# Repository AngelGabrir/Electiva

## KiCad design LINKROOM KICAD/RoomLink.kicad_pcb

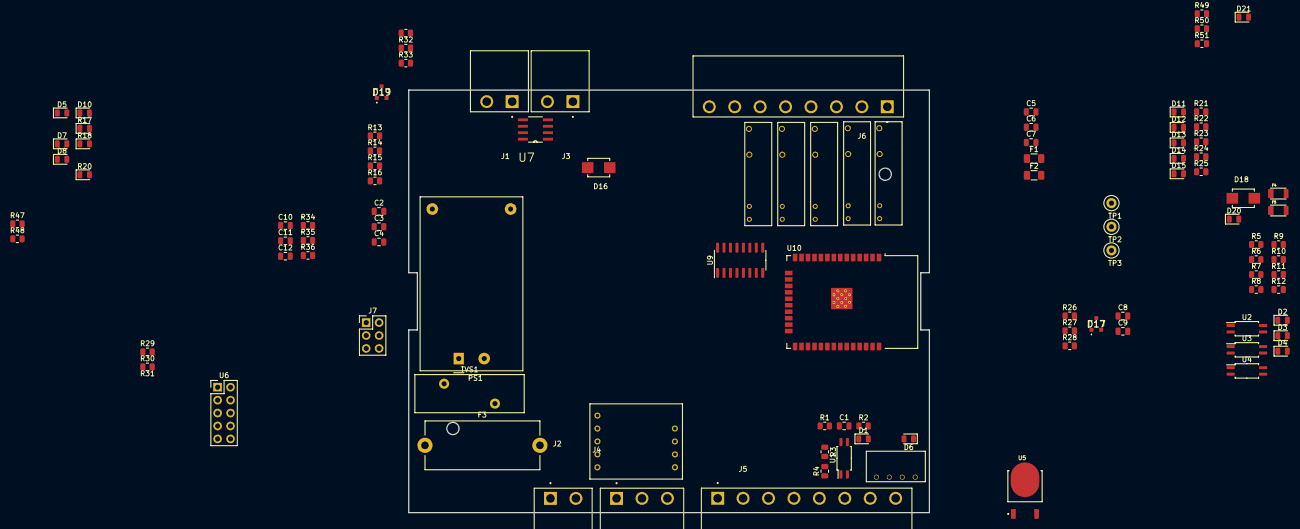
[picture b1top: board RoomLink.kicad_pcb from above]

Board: 4 copper layers, 102.4 x 83.1 mm, 105 parts (0 on the bottom side), 88 nets, no tracks yet.

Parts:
C1, C2, C3, C4, C10, C12: 0.1uF; C_0805_2012Metric
C5: 0.33uF/25V; C_0805_2012Metric
C6: 2.2uF/25V; C_0805_2012Metric
C7: 47uF/10V; C_0805_2012Metric
C8: 1uF/25V; C_0805_2012Metric
C9: 0.1uF/50V; C_0805_2012Metric
C11: 22uF; C_0805_2012Metric
D1, D2, D3, D4, D11, D12, D13, D14, D15, D20: LED; LED_0805_2012Metric
D5, D6: 1SMA5918BT3G; D_0805_2012Metric
D7, D8, D10, D21: LED; D_0805_2012Metric
D16, D18: SMBJ12CA; DIOM4336X265N
D17, D19: SM712-02HTG; SM71202HTG
F1, F2: PTS120660V010; Fuse_1206_3216Metric
F3: Fuse; Fuseholder_Cylinder-5x20mm_Stelvio-Kontek_PTF78_Horizontal_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
F4, F5: PTS120660V010; RESC3115X65N
J1, J2, J3: TBP04R12-500-02BE; CUI_TBP04R12-500-02BE
J4: TBP04R12-500-03GR; CUI_TBP04R12-500-03GR
J5, J6: TBP04R12-500-08GR; CUI_TBP04R12-500-08GR
J7: PinHeader_2x03_P2.54mm_Vertical
K1, K2, K3, K4, K5: AZ921
PS1: HLK-PM12; Converter_ACDC_HiLink_HLK-PMxx
R1, R7, R11, R15: 10K; R_0805_2012Metric
R2, R8, R12, R16, R47: 470; R_0805_2012Metric
R3, R5, R9, R13: 330; R_0805_2012Metric
R4, R6, R10, R14: 10; R_0805_2012Metric
R17, R18: R; D_0805_2012Metric
R20: 470; D_0805_2012Metric
R21, R22, R23, R24, R25: R; R_0805_2012Metric
R26, R27, R28: 10/1%; R_0805_2012Metric
R29, R30, R31, R32, R33: 2.2K; R_0805_2012Metric
R34, R35, R48, R49, R50: 100K; R_0805_2012Metric
R36: 22K; R_0805_2012Metric
R51: 1K; R_0805_2012Metric
TP1, TP2, TP3: TestPoint; TestPoint_Loop_D1.80mm_Drill1.0mm_Beaded
TVS1: RV_Disc_D21.5mm_W7.5mm_P10mm
U1, U2, U3, U4: FODM214; SOP-4_4.4x2.6mm_P1.27mm
U5: NJM2885DL1-33-TE1; DPAK228P968X238-4N
U6: PinHeader_2x05_P2.54mm_Vertical
U7: SP485ECN-L; SOIC127P600X175-8N
U8: TD521D485H-E
U9: ULN2003A; SOIC-16_3.9x9.9mm_P1.27mm
U10: ESP32-WROOM-32
U11: B0303S; B0505S-W2R2

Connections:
+3V3: D6.1 (A), R3.1, R5.1, R9.1, R13.1, U11.4 (OUT+)
+12V: C5.1, F2.2, K1.1, K2.1, K3.1, K4.1, K5.1, PS1.4 (+Vout), R21.2, R22.2, R23.2, R24.2, R25.2, TP3.1, U5.1 (VI)
/Smart-Control-HVAC/CON-A-: F4.2, J4.2
/Smart-Control-HVAC/CON-B+: F5.2, J4.3
/Smart-Control-HVAC/CON-DC+: F2.1, J1.1, R18.1
/Smart-Control-HVAC/CON-DC-: D8.1 (K), F1.1, J1.2
/Smart-Control-HVAC/CON-FAN1: J6.7, K3.4
/Smart-Control-HVAC/CON-FAN2: J6.6, K4.4
/Smart-Control-HVAC/CON-FAN3: J6.5, K5.4
/Smart-Control-HVAC/CON-FAN-C: J6.8, K3.3, K4.3, K5.3
/Smart-Control-HVAC/CON-IN1+: J5.8, U1.2
/Smart-Control-HVAC/CON-IN1-: J5.7, R4.1
/Smart-Control-HVAC/CON-IN2+: J5.6, U3.2
/Smart-Control-HVAC/CON-IN2-: J5.5, R10.1
/Smart-Control-HVAC/CON-IN3+: J5.4, U2.2
/Smart-Control-HVAC/CON-IN3-: J5.3, R6.1
/Smart-Control-HVAC/CON-IN4+: J5.2, U4.2
/Smart-Control-HVAC/CON-IN4-: J5.1, R14.1
/Smart-Control-HVAC/CON-L1: F3.1, J2.1
/Smart-Control-HVAC/CON-LCDA-: J3.1, R28.2
/Smart-Control-HVAC/CON-LCDB+: J3.2, R27.2
/Smart-Control-HVAC/CON-NEUT: J2.2, PS1.1 (AC/L), TVS1.2
/Smart-Control-HVAC/CON-OUT1A: J6.3, K1.4
/Smart-Control-HVAC/CON-OUT1B: J6.4, K1.3
/Smart-Control-HVAC/CON-OUT2A: J6.1, K2.4
/Smart-Control-HVAC/CON-OUT2B: J6.2, K2.3
/Smart-Control-HVAC/CONTROL/COM_RS485_LCD: R26.1, U10.6 (IO34)
/Smart-Control-HVAC/CONTROL/CON_RS485_eXT: U8.5 (CON), U10.7 (IO35)
/Smart-Control-HVAC/CONTROL/INPUT_1_MICRO: C1.1, D1.1 (K), R1.2, U1.4, U10.25 (IO0)
/Smart-Control-HVAC/CONTROL/INPUT_2_MICRO: C3.1, D3.1 (K), R11.2, U3.4, U10.29 (IO5)
/Smart-Control-HVAC/CONTROL/INPUT_3_MICRO: C2.1, D2.1 (K), R7.2, U2.4, U10.26 (IO4)
/Smart-Control-HVAC/CONTROL/INPUT_4_MICRO: C4.1, D4.1 (K), R15.2, U4.4, U10.24 (IO2)
/Smart-Control-HVAC/CONTROL/RLY_FAN1_MICRO: U9.5 (I5), U10.10 (IO25)
/Smart-Control-HVAC/CONTROL/RLY_FAN2_MICRO: U9.4 (I4), U10.11 (IO26)
/Smart-Control-HVAC/CONTROL/RLY_FAN3_MICRO: U9.3 (I3), U10.12 (IO27)
/Smart-Control-HVAC/CONTROL/RLY_OUT1_MICRO: U9.1 (I1), U10.36 (IO22)
/Smart-Control-HVAC/CONTROL/RLY_OUT2_MICRO: U9.2 (I2), U10.37 (IO23)
/Smart-Control-HVAC/CONTROL/Rx_RS485_eXT: U8.4 (RXD), U10.34 (RXD0/IO3)
/Smart-Control-HVAC/CONTROL/Rx_RS485_lcd: U7.4 (DI), U10.27 (IO16)
/Smart-Control-HVAC/CONTROL/Tx_RS485_LCD: U7.1 (RO), U10.28 (IO17)
/Smart-Control-HVAC/CONTROL/Tx_RS485_eXT: U8.3 (TXD), U10.35 (TXD0/IO1)
/Smart-Control-HVAC/RGND: D19.3, J4.1, R33.1, U8.10 (RGND)
EN: C10.2, R35.2, R36.2, U6.10 (EN), U10.3 (EN)
GND: C1.2, C2.2, C3.2, C4.2, C5.2, C6.2, C7.2, C8.2, C9.2, C11.2, C12.2, D5.2 (C), D6.2 (C), D7.1 (K), D10.1 (K), D17.3, F1.2, J7.5, PS1.3 (-Vout), TP2.1, U1.3, U2.3, U3.3, U4.3, U5.2 (GND), U6.3 (GND), U6.9 (GND), U7.5 (GND), U8.2 (GND), U9.8 (GND), U10.1 (GND), U10.15 (GND), U10.38 (GND), U10.39 (GND), U11.1 (IN-)
GNDA: R4.2, R6.2, R10.2, R14.2, U11.3 (OUT-)
MTCLK: R49.2, U6.4 (MTCLK), U10.16 (IO13)
MTD0: R50.2, U6.6 (MTD0), U10.23 (IO15)
MTD1: R34.2, U6.8 (MTD1), U10.14 (IO12)
MTMS: R48.2, U6.2 (MTMS), U10.13 (IO14)
unnamed: D1.2 (A), R2.2
unnamed: D2.2 (A), R8.2
unnamed: D3.2 (A), R12.2
unnamed: D4.2 (A), R16.2
unnamed: D7.2 (A), R17.2
unnamed: D8.2 (A), R18.2
unnamed: D10.2 (A), R20.2
unnamed: D11.2 (A), R21.1
unnamed: D11.1 (K), K1.2, U9.16 (O1)
unnamed: D12.2 (A), R22.1
unnamed: D12.1 (K), K2.2, U9.15 (O2)
unnamed: D13.2 (A), R23.1
unnamed: D13.1 (K), K3.2, U9.14 (O3)
unnamed: D14.2 (A), R24.1
unnamed: D14.1 (K), K4.2, U9.13 (O4)
unnamed: D15.2 (A), R25.1
unnamed: D15.1 (K), K5.2, U9.12 (O5)
unnamed: D20.2 (A), R29.2
unnamed: D21.2 (A), R47.1
unnamed: D21.1 (K), U10.9 (IO33)
unnamed: F4.1, R31.2
unnamed: F5.1, R32.2
unnamed: F3.2, PS1.2 (AC/N), TVS1.1
unnamed: R3.2, U1.1
unnamed: R5.2, U2.1
unnamed: R9.2, U3.1
unnamed: R13.2, U4.1
unnamed: R51.2, U6.1 (Vin)
unnamed: D16.1, D17.1, D17.2, R27.1, U7.6 (A)
unnamed: D16.2, R28.1, U7.7 (B)
unnamed: R26.2, U7.2 (~RE), U7.3 (DE)
unnamed: D18.2, D19.2, R30.2, R31.1, U8.9 (A)
unnamed: D18.1, D19.1, R32.1, R33.2, U8.8 (B)
unnamed: R29.1, R30.1, U8.7 (Vo)
unnamed: J7.2, U10.30 (IO18)
unnamed: J7.4, U10.31 (IO19)
unnamed: J7.6, U10.33 (IO21)
unnamed: J7.3, U10.8 (IO32)
VDD: C6.1, C7.1, C8.1, C9.1, C10.1, C11.1, C12.1, D5.1 (A), J7.1, R1.1, R2.1, R7.1, R8.1, R11.1, R12.1, R15.1, R16.1, R17.1, R20.1, R34.1, R35.1, R36.1, R47.2, R48.1, R49.1, R50.1, R51.1, TP1.1, U5.3 (VO), U7.8 (VCC), U8.1 (VCC), U10.2 (VDD), U11.2 (IN+)

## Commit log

2023-05-19 Primera tarea Electiva
2023-06-08 logo PDF
2023-06-08 Norma
2023-06-11 ESP32
2023-07-03 kicad
2023-07-03 Diseño
